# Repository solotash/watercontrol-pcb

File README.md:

# WaterControl - PCB

A simple PCB for controlling two small 12V pumps and two capacitive soil moisture sensors with an esp-12f, powered by a usual 12V power supply (eg for external HDD drives).

If you have any questions, open an issue, Ill answer gladly! 

For gerber files, look at the [release(s)](https://github.com/mqus/watercontrol-pcb/releases)

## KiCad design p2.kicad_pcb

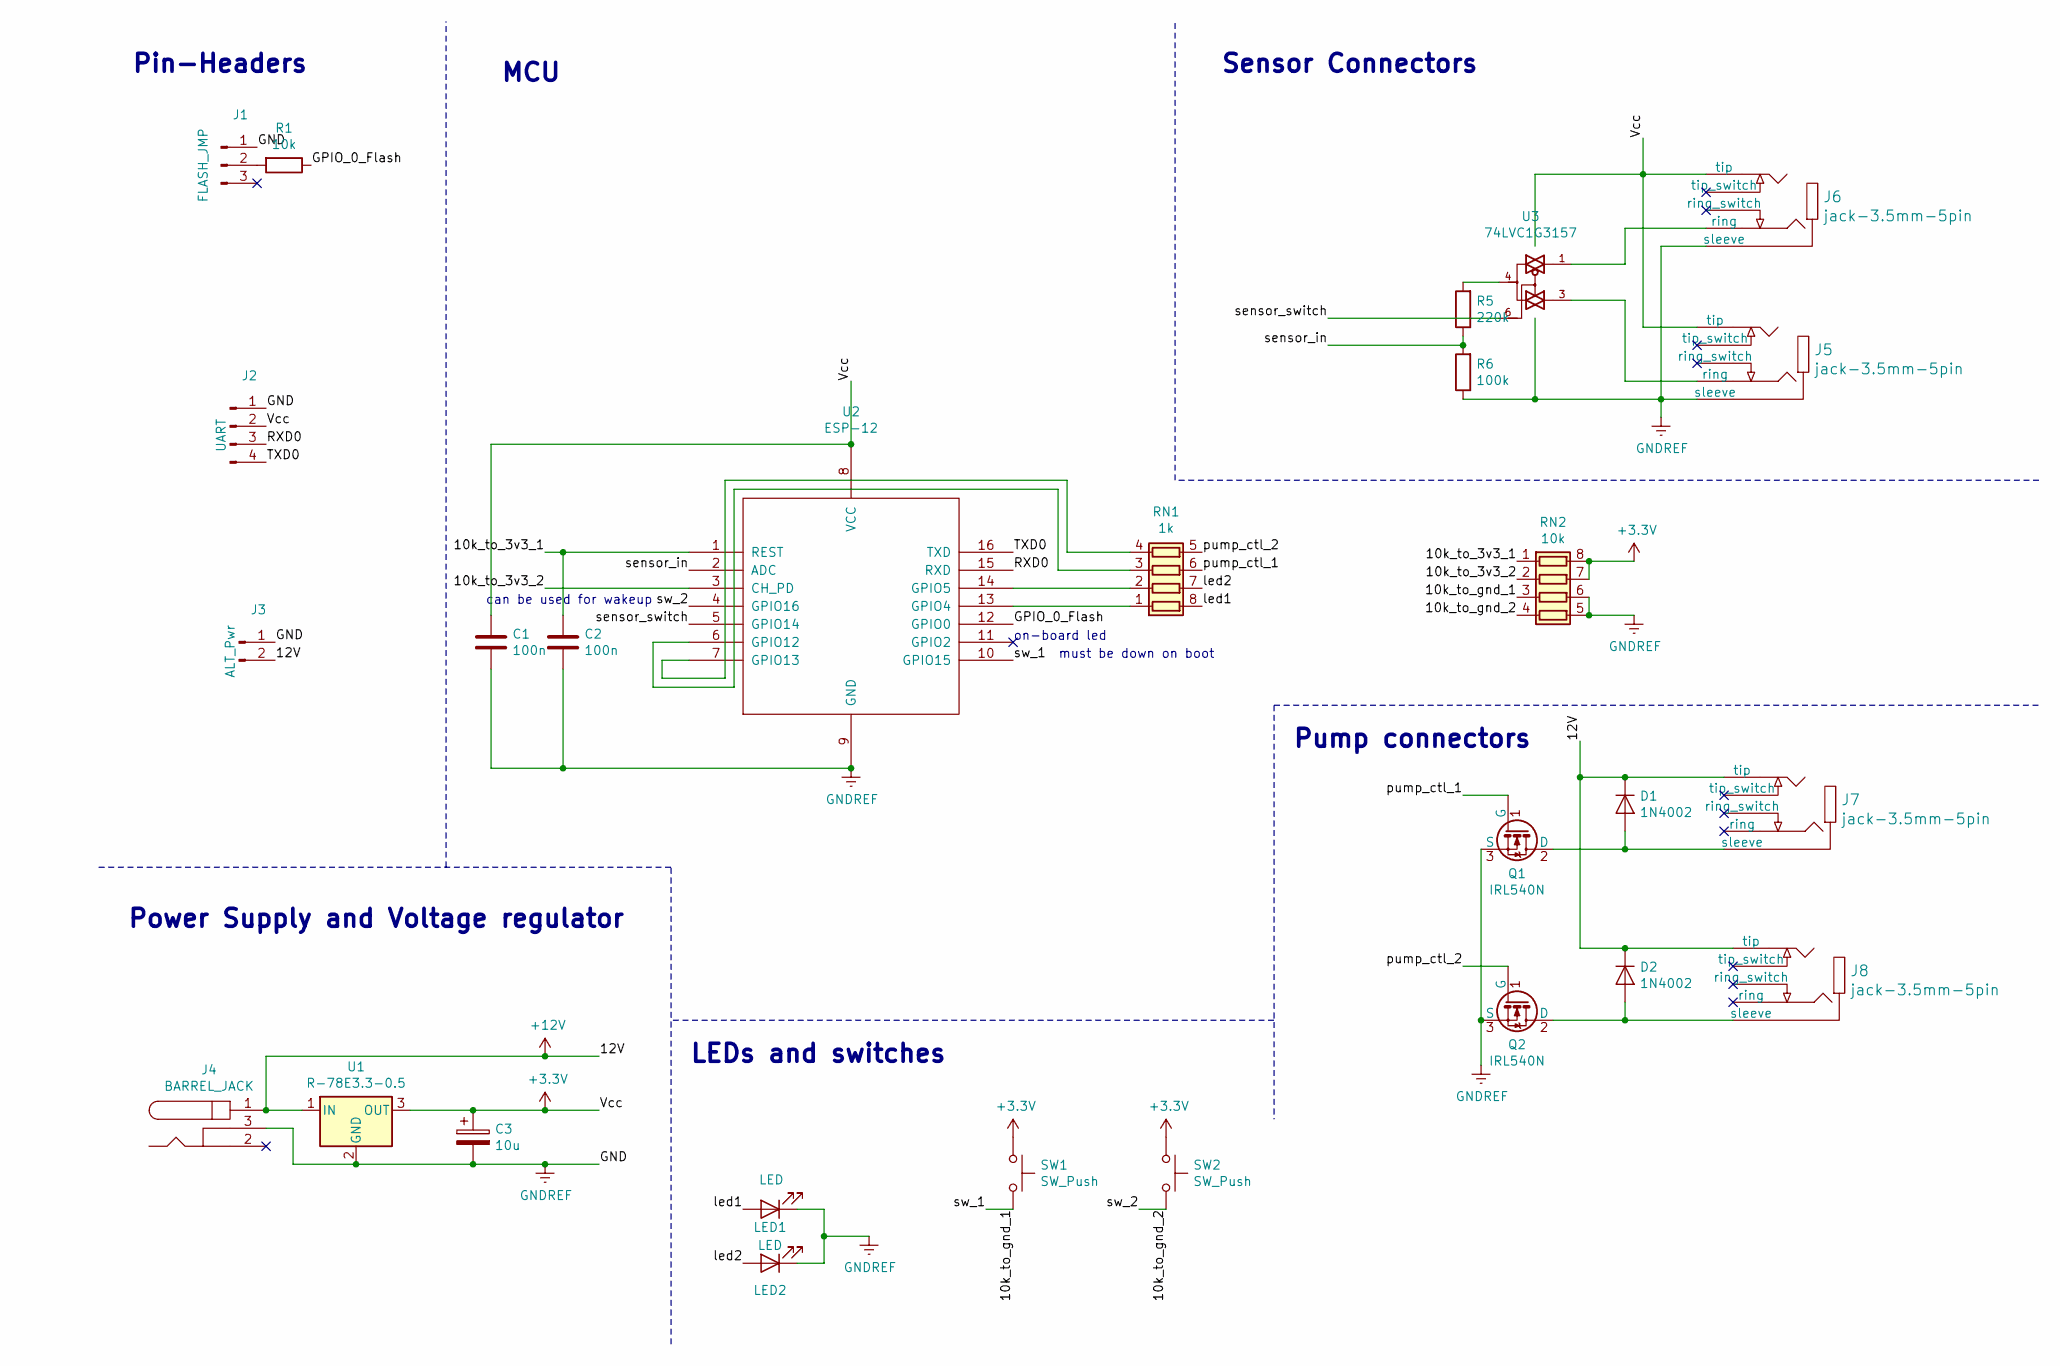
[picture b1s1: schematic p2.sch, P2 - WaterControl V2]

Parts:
C1, C2: 100n; C_Disc_D5.0mm_W2.5mm_P5.00mm
C3: 10u; CP_Radial_Tantal_D5.0mm_P2.50mm
D1, D2: 1N4002; D_A-405_P10.16mm_Horizontal
J1: FLASH_JMP; PinHeader_2.54mm_1x3_short
J2: UART; PinHeader_1x04_P2.54mm_Vertical
J3: ALT_Pwr; PinHeader_1x02_P2.54mm_Vertical
J4: BARREL_JACK; Barrel_Jack_5.5_2.1mm
J5, J6, J7, J8: jack-3.5mm-5pin; 3.5mm_5pin_jack
LED1, LED2: LED; LED_D3.0mm_Horizontal_O1.27mm_Z2.0mm_Clear
Q1: IRL540N; TO-220-3_Horizontal_TabUp
Q2: IRL540N; TO-220-3_Horizontal_TabDown
R1: 10k; R_Axial_DIN0207_L6.3mm_D2.5mm_P7.62mm_Horizontal
R5: 220k; R_Axial_DIN0207_L6.3mm_D2.5mm_P7.62mm_Horizontal
R6: 100k; R_Axial_DIN0207_L6.3mm_D2.5mm_P7.62mm_Horizontal
RN1: 1k; ResistorArrayx4-27185436
RN2: 10k; ResistorArrayx4-18726345
SW1, SW2: SW_Push; SW_Tactile_SPST_Angled_PTS645Vx58-2LFS
U1: R-78E3.3-0.5; DCDC-Conv_Recom_R-78Exx-0.5
U2: ESP-12
U3: 74LVC1G3157; SOT-363_SC-70-6_Handsoldering

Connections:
+3V3: C1.1, C3.1, J2.2, J5.2 (tip), J6.2 (tip), RN2.7 (R2.2), RN2.8 (R1.2), SW1.1, SW2.1, U1.3 (OUT), U2.8 (VCC), U3.5 (VCC)
+12V: D1.1 (K), D2.1 (K), J3.2, J4.1, J7.2 (tip), J8.2 (tip), U1.1 (IN)
/10k_to_3v3_1: C2.1, RN2.1 (R1.1), U2.1 (REST)
/10k_to_3v3_2: RN2.2 (R2.1), U2.3 (CH_PD)
/10k_to_gnd_1: RN2.3 (R3.1), SW1.2, U2.10 (GPIO15)
/10k_to_gnd_2: RN2.4 (R4.1), SW2.2, U2.4 (GPIO16)
/GPIO_0_Flash: R1.1, U2.12 (GPIO0)
/RXD0: J2.3, U2.15 (RXD)
/TXD0: J2.4, U2.16 (TXD)
/led1: LED1.2 (A), RN1.8 (R1.2)
/led2: LED2.2 (A), RN1.7 (R2.2)
/pump_ctl_1: Q1.1 (G), RN1.6 (R3.2)
/pump_ctl_2: Q2.1 (G), RN1.5 (R4.2)
/sensor_in: R5.1, R6.2, U2.2 (ADC)
/sensor_switch: U2.5 (GPIO14), U3.6
GND: C1.2, C2.2, C3.2, J1.1, J2.1, J3.1, J4.3, J5.1 (sleeve), J6.1 (sleeve), LED1.1 (K), LED2.1 (K), Q1.3 (S), Q2.3 (S), R6.1, RN2.5 (R4.2), RN2.6 (R3.2), U1.2 (GND), U2.9 (GND), U3.2 (GND)
unnamed: D1.2 (A), J7.1 (sleeve), Q1.2 (D)
unnamed: D2.2 (A), J8.1 (sleeve), Q2.2 (D)
unnamed: J1.2, R1.2
unnamed: J5.3 (ring), U3.3
unnamed: J6.3 (ring), U3.1
unnamed: R5.2, U3.4
unnamed: RN1.1 (R1.1), U2.13 (GPIO4)
unnamed: RN1.2 (R2.1), U2.14 (GPIO5)
unnamed: RN1.3 (R3.1), U2.6 (GPIO12)
unnamed: RN1.4 (R4.1), U2.7 (GPIO13)

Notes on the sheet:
on-board led
must be down on boot
Pin-Headers
Power Supply and Voltage regulator
LEDs and switches
Pump connectors
Sensor Connectors
MCU
can be used for wakeup

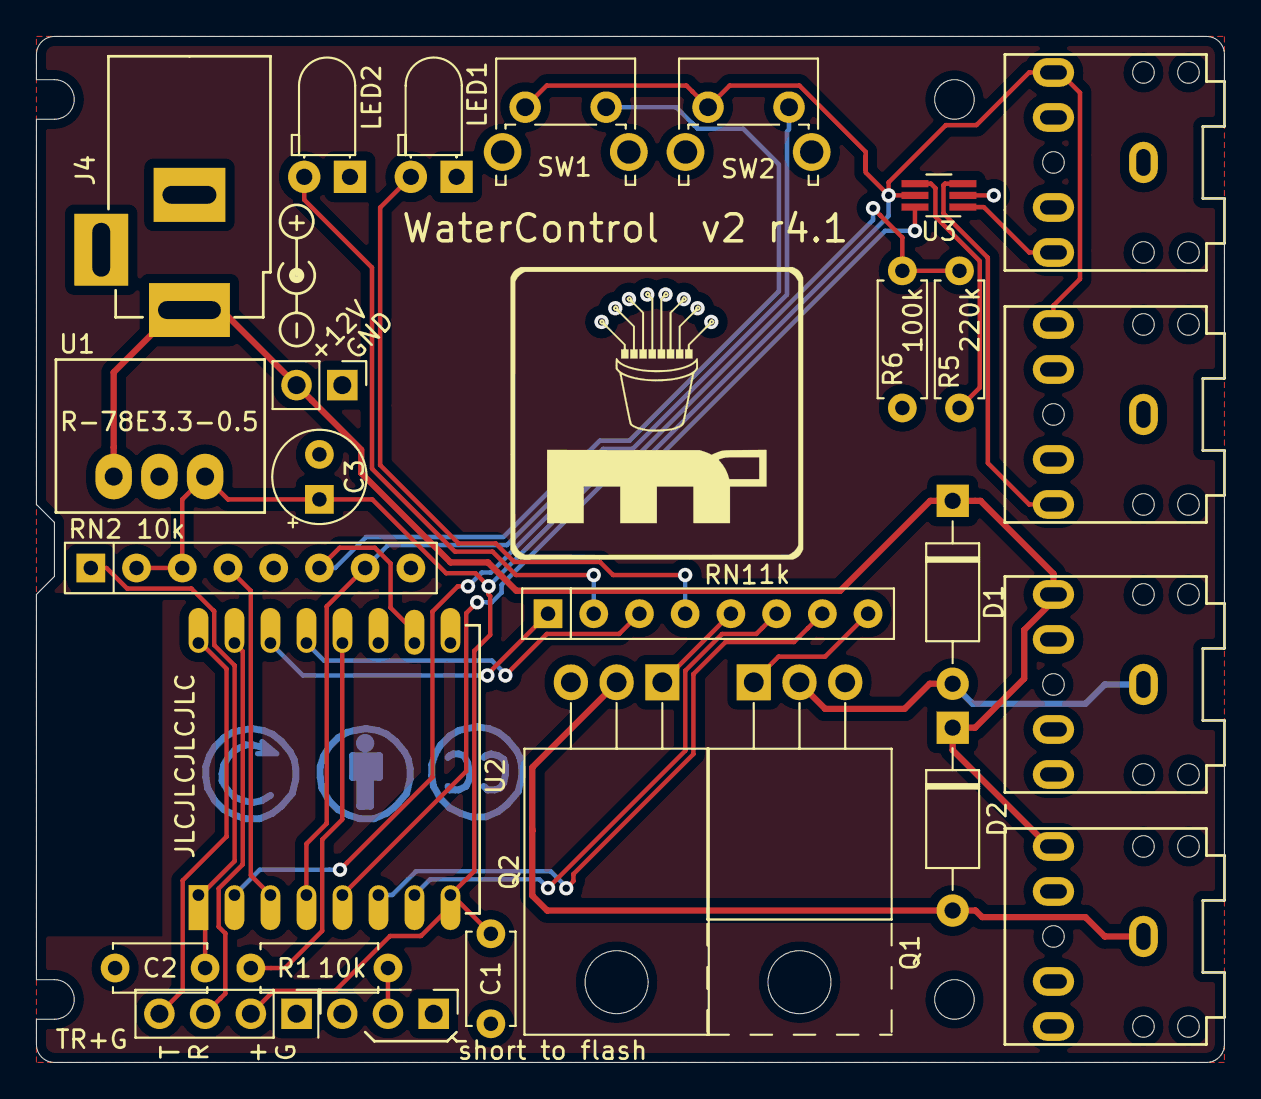
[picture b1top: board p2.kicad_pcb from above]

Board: 2 copper layers, 66.0 x 57.0 mm, 27 parts (0 on the bottom side), 26 nets.

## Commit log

2017-04-24 initial commit, ref 3.3
2017-04-25 update pcb to rev 1.3 (added copper pours)
2017-04-25 rounded corners and edge-screwholes
2017-04-29 now it's ready.
2017-06-10 current state sync
2019-08-25 rev4.1 - switched to capacitive sensors by including a multiplexer, added another switch, rotated both.
2019-08-25 add license
2019-08-25 ignore gerber/drill files
